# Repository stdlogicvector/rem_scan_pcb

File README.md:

# rem_scan_pcb

## An open source scan controller for SEMs

- Firmware: https://github.com/stdlogicvector/rem_scan
- GUI: https://github.com/stdlogicvector/rem_scan_gui

This PCB features two 16bit DACs to steer the electron beam of an SEM and two 16bit ADCs to acquire the image signal from up to two detectors.

It can be controlled via USB. The FTDI chip provides a virtual comport, a fast FIFO connection and a JTAG port for flashing the gateware.
Currently, only the serial port is supported in the gateware and the GUI.

Additionally, a VGA monitor can be connected for a live view of the image.
On PCBv1, only the internal blockram is used. This limits the resolution to 100x75 pixels. The image is upscaled to 800x600.

PCBv2 has external RAM and allows a native resolution of 800x600.

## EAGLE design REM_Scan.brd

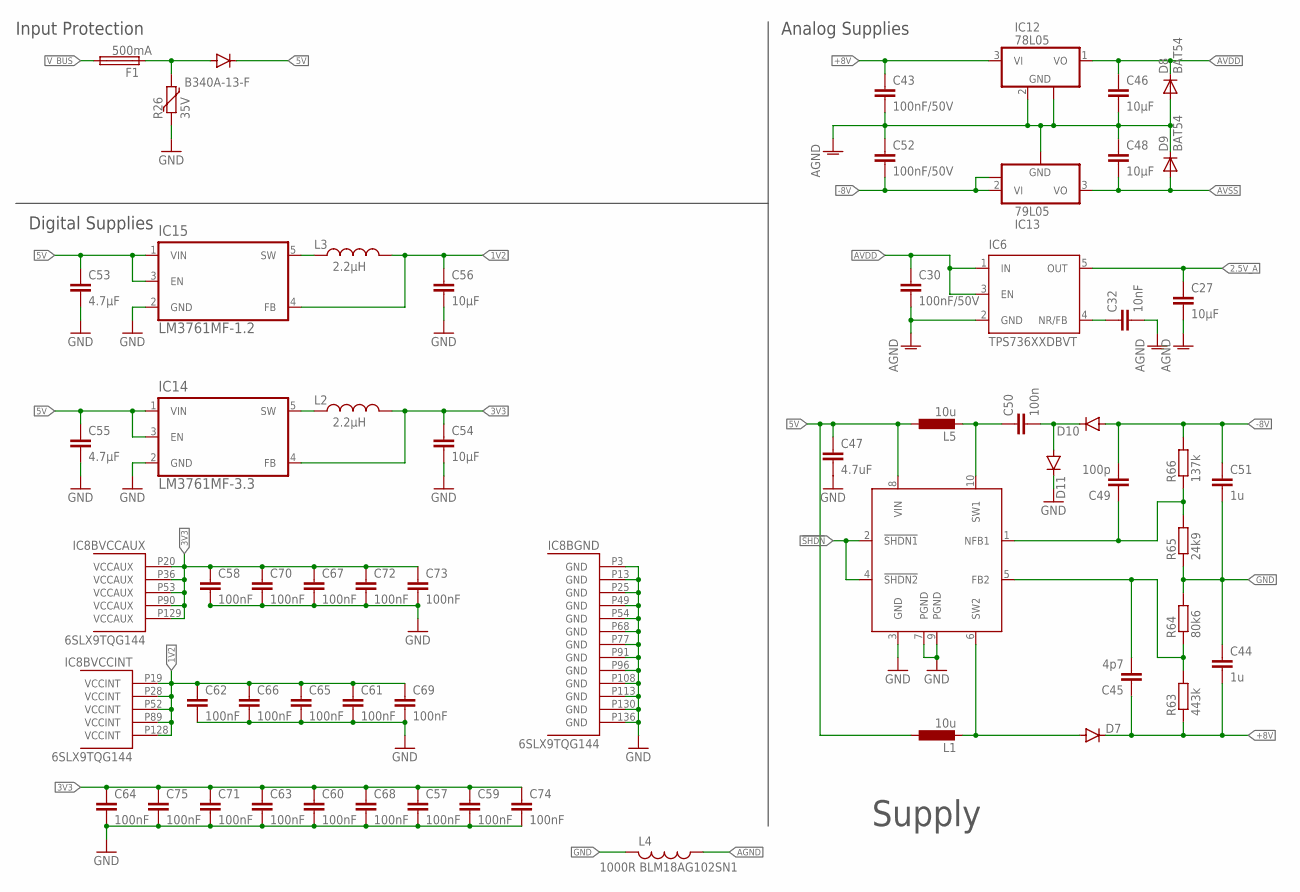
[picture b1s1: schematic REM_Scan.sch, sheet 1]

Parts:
C27, C46, C48: 10µF; C0603; FARNELL 2497051
C30, C43, C52: 100nF/50V; C0603
C32: 10nF; C0603
C44, C51: 1u; C1206; DIGIKEY 587-5596-1-ND
C45: 4p7; C0603
C47: 4.7uF; C3225
C49: 100p; C0603
C50: 100n; C0603
C53, C55: 4.7µF; C0603
C54, C56: 10µF; C0603
C57, C58, C59, C60, C61, C62, C63, C64, C65, C66, C67, C68, C69, C70, C71, C72, C73, C74, C75: 100nF; C0603
D3: B340A-13-F; DO214AA; FARNELL 1843668
D7, D10, D11: DIODE-SOD323-W; SOD323-W; DIGIKEY 1514-CMDSH05-4TRPBFREECT-ND
D8, D9: BAT54; SOD323-W; FARNELL 1459033
F1: 500mA; 1812; DIGIKEY F8132CT-ND
IC6: TPS736XXDBVT; SOT23-DBV
IC8: 6SLX9TQG144; TQ144; DIGIKEY 122-1747-ND
IC12: 78L05; SOT89; FARNELL 1366573
IC13: 79L05; SOT89; FARNELL 1467770
IC14: LM3761MF-3.3; SOT95P284X122-5N; FARNELL 1685767
IC15: LM3761MF-1.2; SOT95P284X122-5N; FARNELL 1685653
IC16: LT1945; MSOP10; DIGIKEY 505-LT1945EMS#PBF-ND
L1, L5: 10u; L3225P; DIGIKEY 445-174925-1-ND
L2, L3: 2.2µH; SO3314; FARNELL 2457514
L4: 1000R BLM18AG102SN1; L2012C; FARNELL 1515671
R26: 35V; R1206; DIGIKEY 118-ZV25K1206201NIR1CT-ND
R63: 443k; R0603
R64: 80k6; R0603
R65: 24k9; R0603
R66: 137k; R0603

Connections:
1V2: C56.1, C61.1, C62.1, C65.1, C66.1, C69.1, IC8.P19 (VCCINT), IC8.P28 (VCCINT), IC8.P52 (VCCINT), IC8.P89 (VCCINT), IC8.P128 (VCCINT), IC15.4 (FB), L3.2
2.5V_A: C27.1, IC6.5 (OUT); also elsewhere on the board
3V3: C54.1, C57.1, C58.1, C59.1, C60.1, C63.1, C64.1, C67.1, C68.1, C70.1, C71.1, C72.1, C73.1, C74.1, C75.1, IC8.P20 (VCCAUX), IC8.P36 (VCCAUX), IC8.P53 (VCCAUX), IC8.P90 (VCCAUX), IC8.P129 (VCCAUX), IC14.4 (FB), L2.2; also elsewhere on the board
5V: C47.1, C53.1, C55.1, D3.C, IC14.1 (VIN), IC14.3 (EN), IC15.1 (VIN), IC15.3 (EN), IC16.8 (VIN), L1.1, L5.1; also elsewhere on the board
!SHDN: IC16.2 (!SHDN1), IC16.4 (!SHDN2); also elsewhere on the board
+8V: C43.1, C44.2, C45.1, D7.C, IC12.3 (VI), R63.1; also elsewhere on the board
-8V: C49.2, C51.1, C52.2, D10.A, IC13.2 (VI), IC13.2@1 (VIN), R66.2
AGND: C27.2, C30.2, C32.2, C43.2, C46.2, C48.1, C52.1, D8.A, D9.C, IC6.2 (GND), IC12.2 (GND), IC12.2@1 (GND), IC13.1 (GND), L4.1; also elsewhere on the board
AVDD: C30.1, C46.1, D8.C, IC6.1 (IN), IC6.3 (EN), IC12.1 (VO); also elsewhere on the board
AVSS: C48.2, D9.A, IC13.3 (VO); also elsewhere on the board
GND: C44.1, C47.2, C51.2, C53.2, C54.2, C55.2, C56.2, C57.2, C58.2, C59.2, C60.2, C61.2, C62.2, C63.2, C64.2, C65.2, C66.2, C67.2, C68.2, C69.2, C70.2, C71.2, C72.2, C73.2, C74.2, C75.2, D11.C, IC8.P3 (GND), IC8.P13 (GND), IC8.P25 (GND), IC8.P49 (GND), IC8.P54 (GND), IC8.P68 (GND), IC8.P77 (GND), IC8.P91 (GND), IC8.P96 (GND), IC8.P108 (GND), IC8.P113 (GND), IC8.P130 (GND), IC8.P136 (GND), IC14.2 (GND), IC15.2 (GND), IC16.3 (GND), IC16.7 (PGND), IC16.9 (PGND), L4.2, R26.1, R64.2, R65.1; also elsewhere on the board
unnamed: IC15.5 (SW), L3.1
unnamed: C32.1, IC6.4 (NR/FB)
unnamed: C50.1, IC16.10 (SW1), L5.2
unnamed: C50.2, D10.C, D11.A
unnamed: D7.A, IC16.6 (SW2), L1.2
unnamed: C49.1, IC16.1 (NFB1), R65.2, R66.1
unnamed: C45.2, IC16.5 (FB2), R63.2, R64.1
unnamed: IC14.5 (SW), L2.1
SUPPLY_SEC: D3.A, F1.1, R26.2
V_BUS: F1.2; also elsewhere on the board

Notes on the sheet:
Input Protection
Supply
Digital Supplies
Analog Supplies

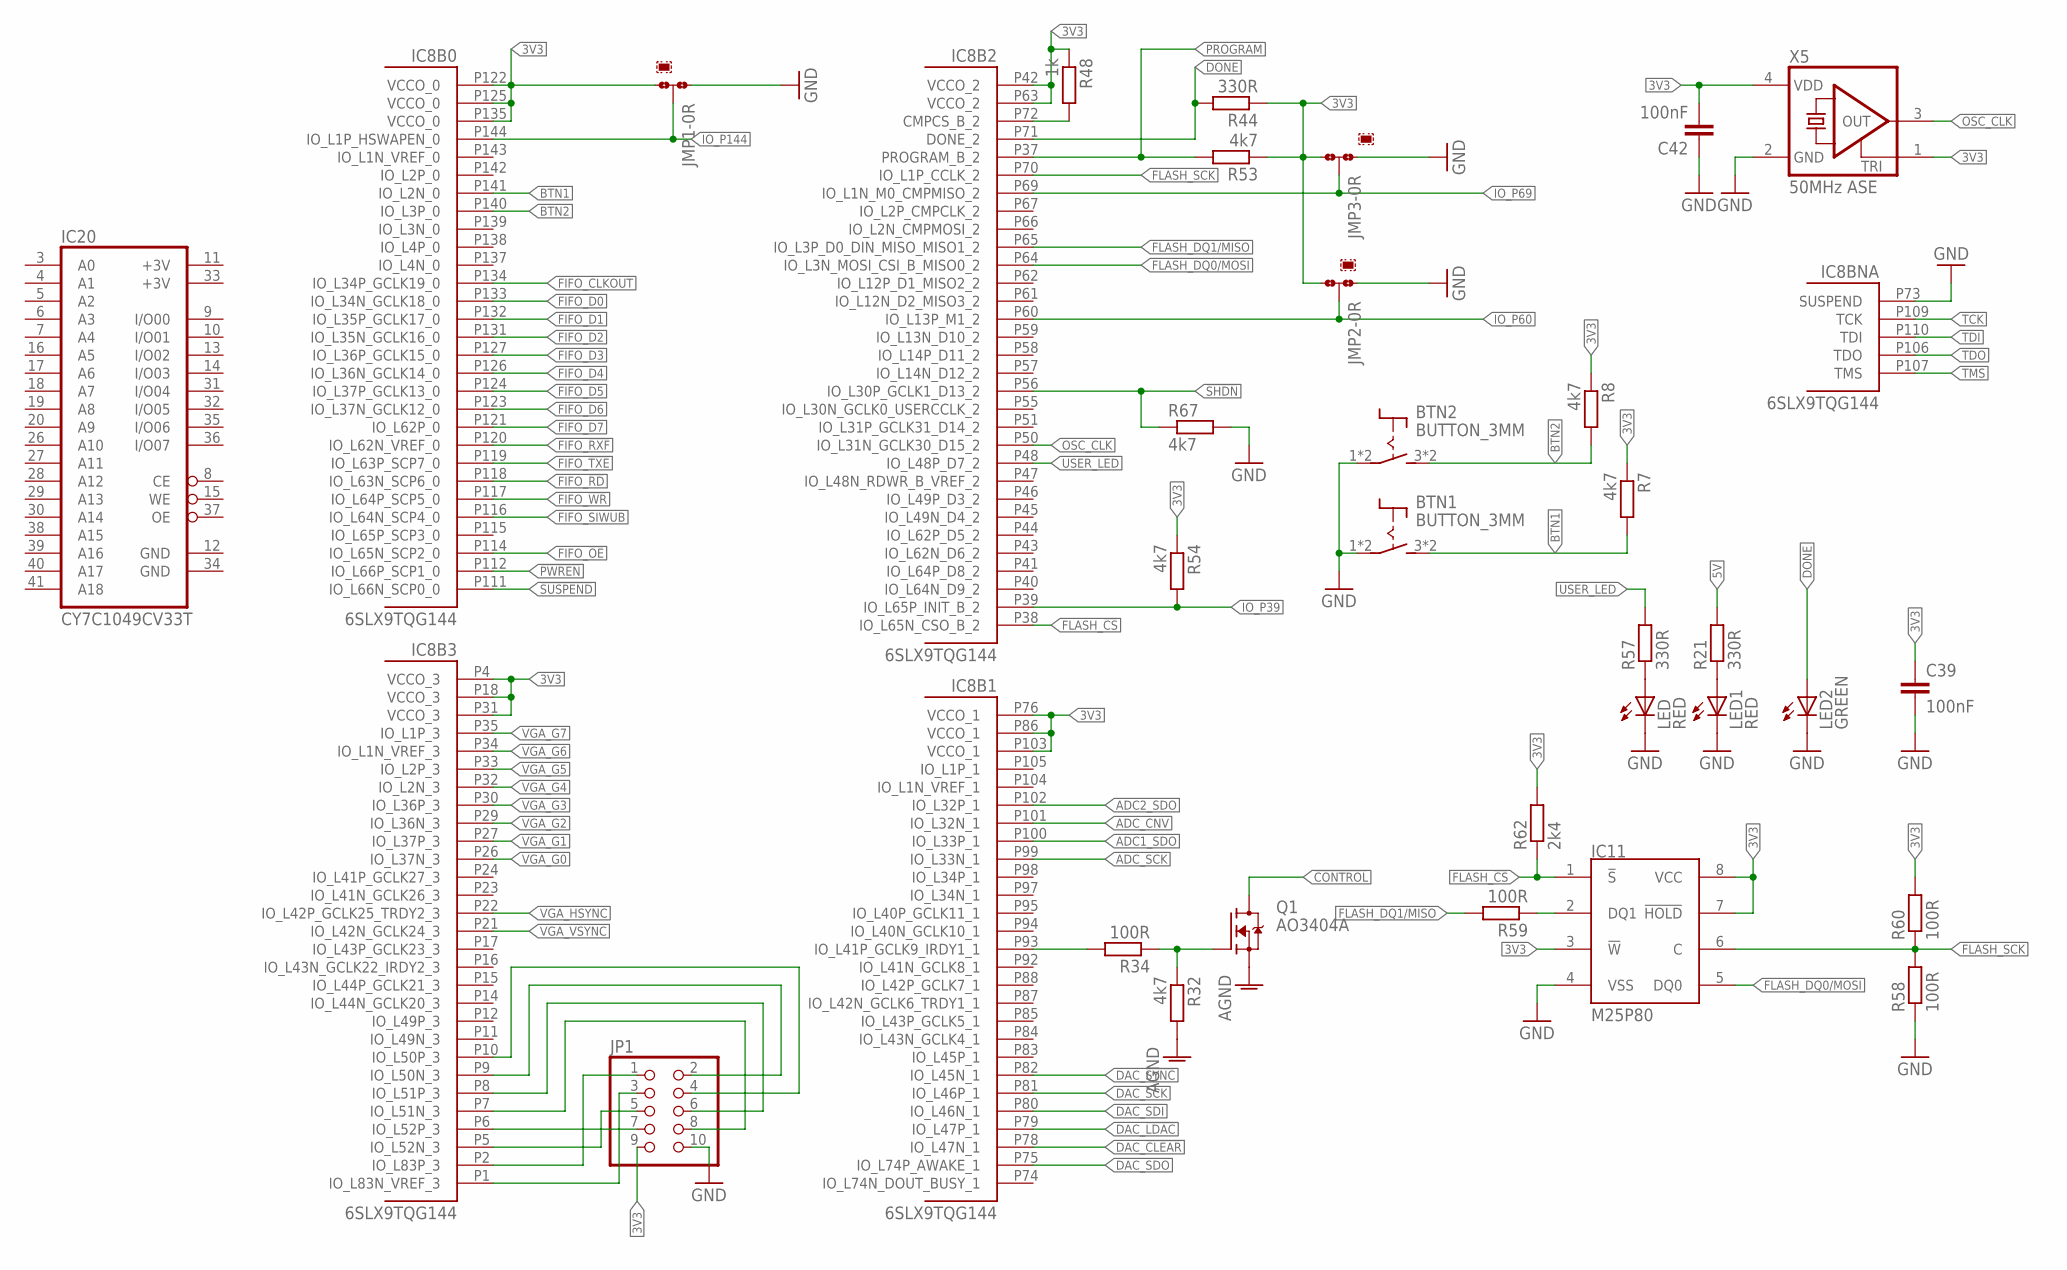
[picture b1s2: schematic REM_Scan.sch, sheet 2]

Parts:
BTN1, BTN2: BUTTON_3MM
C39, C42: 100nF; C0603
IC8: 6SLX9TQG144; TQ144; DIGIKEY 122-1747-ND
IC11: M25P80; SO-08
IC20: CY7C1049CV33T; TSOPII-Z44
JMP1, JMP2, JMP3: 1k; A0R-JMP
JP1: PINHD-2X5; 2X05
LED, LED1: RED; CHIP-LED0603; FARNELL 1685068
LED2: GREEN; CHIP-LED0603; FARNELL 1685068
Q1: AO3404A; SOT23; LCSC C30010
R7, R8, R32, R53, R54, R67: 4k7; R0603
R21, R44, R57: 330R; R0603
R34, R58, R59, R60: 100R; R0603
R48: 1k; R0603
R62: 2k4; R0603
X5: 50MHz ASE; ASE; DIGIKEY 535-9577-1-ND

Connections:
3V3: C39.1, C42.2, IC8.P4 (VCCO_3), IC8.P18 (VCCO_3), IC8.P31 (VCCO_3), IC8.P42 (VCCO_2), IC8.P63 (VCCO_2), IC8.P76 (VCCO_1), IC8.P86 (VCCO_1), IC8.P103 (VCCO_1), IC8.P122 (VCCO_0), IC8.P125 (VCCO_0), IC8.P135 (VCCO_0), IC11.3 (!W), IC11.7 (!HOLD), IC11.8 (VCC), JMP1.3, JMP2.3, JMP3.3, JP1.9, R7.1, R8.1, R44.1, R48.1, R53.1, R54.1, R60.2, R62.2, X5.1 (TRI), X5.4 (VDD); also elsewhere on the board
5V: R21.2; also elsewhere on the board
!CONTROL: Q1.3 (D); also elsewhere on the board
!PWREN: IC8.P112 (IO_L66P_SCP1_0); also elsewhere on the board
!SHDN: IC8.P56 (IO_L30P_GCLK1_D13_2), R67.1; also elsewhere on the board
!SUSPEND: IC8.P111 (IO_L66N_SCP0_0); also elsewhere on the board
+3V: IC20.11 (+3V), IC20.33 (+3V)
ADC1_SDO: IC8.P100 (IO_L33P_1); also elsewhere on the board
ADC2_SDO: IC8.P102 (IO_L32P_1); also elsewhere on the board
ADC_CNV: IC8.P101 (IO_L32N_1); also elsewhere on the board
ADC_SCK: IC8.P99 (IO_L33N_1); also elsewhere on the board
AGND: Q1.2 (S), R32.2; also elsewhere on the board
BTN1: BTN1.3 (S), BTN1.4 (S), IC8.P141 (IO_L2N_0), R7.2
BTN2: BTN2.3 (S), BTN2.4 (S), IC8.P140 (IO_L3P_0), R8.2
DAC_!CLEAR: IC8.P78 (IO_L47N_1); also elsewhere on the board
DAC_!LDAC: IC8.P79 (IO_L47P_1); also elsewhere on the board
DAC_!SYNC: IC8.P82 (IO_L45N_1); also elsewhere on the board
DAC_SCK: IC8.P81 (IO_L46P_1); also elsewhere on the board
DAC_SDI: IC8.P80 (IO_L46N_1); also elsewhere on the board
DAC_SDO: IC8.P75 (IO_L74P_AWAKE_1); also elsewhere on the board
DONE: IC8.P71 (DONE_2), LED2.A, R44.2
FIFO_!OE: IC8.P114 (IO_L65N_SCP2_0); also elsewhere on the board
FIFO_!RD: IC8.P118 (IO_L63N_SCP6_0); also elsewhere on the board
FIFO_!RXF: IC8.P120 (IO_L62N_VREF_0); also elsewhere on the board
FIFO_!TXE: IC8.P119 (IO_L63P_SCP7_0); also elsewhere on the board
FIFO_!WR: IC8.P117 (IO_L64P_SCP5_0); also elsewhere on the board
FIFO_CLKOUT: IC8.P134 (IO_L34P_GCLK19_0); also elsewhere on the board
FIFO_D0: IC8.P133 (IO_L34N_GCLK18_0); also elsewhere on the board
FIFO_D1: IC8.P132 (IO_L35P_GCLK17_0); also elsewhere on the board
FIFO_D2: IC8.P131 (IO_L35N_GCLK16_0); also elsewhere on the board
FIFO_D3: IC8.P127 (IO_L36P_GCLK15_0); also elsewhere on the board
FIFO_D4: IC8.P126 (IO_L36N_GCLK14_0); also elsewhere on the board
FIFO_D5: IC8.P124 (IO_L37P_GCLK13_0); also elsewhere on the board
FIFO_D6: IC8.P123 (IO_L37N_GCLK12_0); also elsewhere on the board
FIFO_D7: IC8.P121 (IO_L62P_0); also elsewhere on the board
FIFO_SIWUB: IC8.P116 (IO_L64N_SCP4_0); also elsewhere on the board
FLASH_!CS: IC8.P38 (IO_L65N_CSO_B_2), IC11.1 (!S), R62.1
FLASH_DQ0/MOSI: IC8.P64 (IO_L3N_MOSI_CSI_B_MISO0_2), IC11.5 (DQ0)
FLASH_DQ1/MISO: IC8.P65 (IO_L3P_D0_DIN_MISO_MISO1_2), R59.2
FLASH_SCK: IC8.P70 (IO_L1P_CCLK_2), IC11.6 (C), R58.2, R60.1
GND: BTN1.1, BTN1.2, BTN2.1, BTN2.2, C39.2, C42.1, IC8.P73 (SUSPEND), IC11.4 (VSS), IC20.12 (GND), IC20.34 (GND), JMP1.1, JMP2.1, JMP3.1, JP1.10, LED.C, LED1.C, LED2.C, R58.1, R67.2, X5.2 (GND); also elsewhere on the board
IO_P39: IC8.P39 (IO_L65P_INIT_B_2), R54.2
IO_P60: IC8.P60 (IO_L13P_M1_2), JMP2.2
IO_P69: IC8.P69 (IO_L1N_M0_CMPMISO_2), JMP3.2
IO_P144: IC8.P144 (IO_L1P_HSWAPEN_0), JMP1.2
unnamed: IC11.2 (DQ1), R59.1
unnamed: LED1.A, R21.1
unnamed: Q1.1 (G), R32.1, R34.1
unnamed: IC8.P72 (CMPCS_B_2), R48.2
unnamed: IC8.P93 (IO_L41P_GCLK9_IRDY1_1), R34.2
unnamed: LED.A, R57.1
unnamed: IC8.P6 (IO_L52P_3), JP1.7
unnamed: IC8.P7 (IO_L51N_3), JP1.8
unnamed: IC8.P5 (IO_L52N_3), JP1.5
unnamed: IC8.P8 (IO_L51P_3), JP1.6
unnamed: IC8.P1 (IO_L83N_VREF_3), JP1.3
unnamed: IC8.P2 (IO_L83P_3), JP1.1
unnamed: IC8.P9 (IO_L50N_3), JP1.2
unnamed: IC8.P10 (IO_L50P_3), JP1.4
OSC_CLK: IC8.P50 (IO_L31N_GCLK30_D15_2), X5.3 (OUT)
PROGRAM: IC8.P37 (PROGRAM_B_2), R53.2
TCK: IC8.P109 (TCK); also elsewhere on the board
TDI: IC8.P110 (TDI); also elsewhere on the board
TDO: IC8.P106 (TDO); also elsewhere on the board
TMS: IC8.P107 (TMS); also elsewhere on the board
USER_LED: IC8.P48 (IO_L48P_D7_2), R57.2
VGA_G0: IC8.P26 (IO_L37N_3); also elsewhere on the board
VGA_G1: IC8.P27 (IO_L37P_3); also elsewhere on the board
VGA_G2: IC8.P29 (IO_L36N_3); also elsewhere on the board
VGA_G3: IC8.P30 (IO_L36P_3); also elsewhere on the board
VGA_G4: IC8.P32 (IO_L2N_3); also elsewhere on the board
VGA_G5: IC8.P33 (IO_L2P_3); also elsewhere on the board
VGA_G6: IC8.P34 (IO_L1N_VREF_3); also elsewhere on the board
VGA_G7: IC8.P35 (IO_L1P_3); also elsewhere on the board
VGA_HSYNC: IC8.P22 (IO_L42P_GCLK25_TRDY2_3); also elsewhere on the board
VGA_VSYNC: IC8.P21 (IO_L42N_GCLK24_3); also elsewhere on the board

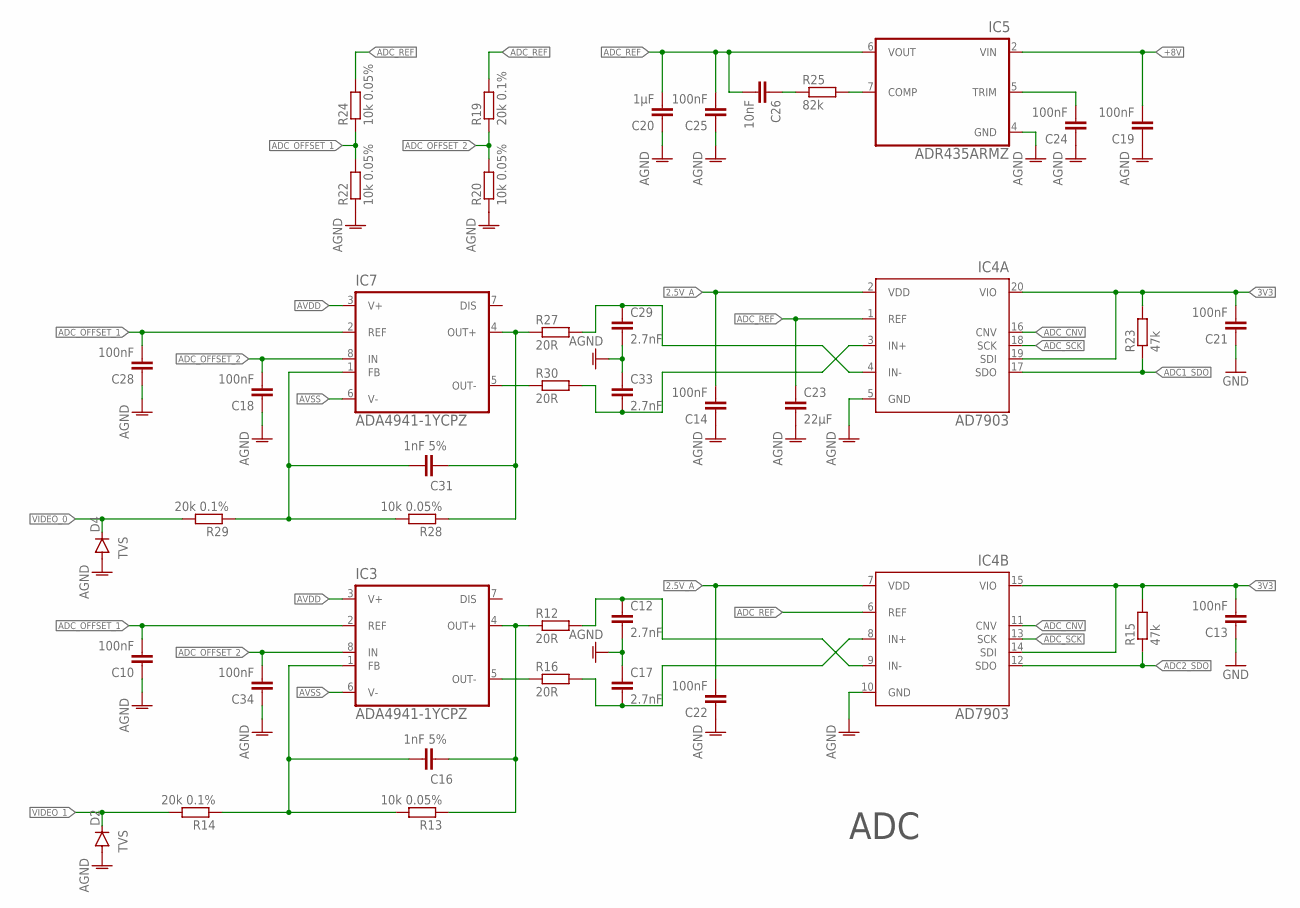
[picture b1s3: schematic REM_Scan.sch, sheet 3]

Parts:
C10, C13, C14, C18, C19, C21, C22, C24, C25, C28, C34: 100nF; C0603
C12, C17, C29, C33: 2.7nF; C0603K; FARNELL 1759094
C16, C31: 1nF 5%; C0603; FARNELL 1789718
C20: 1µF; C0603; FARNELL 2496835
C23: 22µF; C0805K; FARNELL 1845739
C26: 10nF; C0603
D2, D4: TVS; SOD123; DIGIKEY 641-1986-1-ND
IC3, IC7: ADA4941-1YCPZ; LFCSP_VD8_CP-8-2
IC4: AD7903; RQ-20
IC5: ADR435ARMZ; MSOP08
R12, R16, R27, R30: 20R; R0603; FARNELL 9330763
R13, R20, R22, R24, R28: 10k 0.05%; R0603; FARNELL 1688472
R14, R19, R29: 20k 0.1%; R0603; FARNELL 1717605
R15, R23: 47k; R0603; FARNELL 2141566
R25: 82k; R0603; FARNELL 9331573

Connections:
2.5V_A: C14.2, C22.2, IC4.2 (VDD), IC4.7 (VDD); also elsewhere on the board
3V3: C13.2, C21.2, IC4.14 (SDI), IC4.15 (VIO), IC4.19 (SDI), IC4.20 (VIO), R15.2, R23.2; also elsewhere on the board
+8V: C19.2, IC5.2 (VIN); also elsewhere on the board
ADC1_SDO: IC4.17 (SDO), R23.1; also elsewhere on the board
ADC2_SDO: IC4.12 (SDO), R15.1; also elsewhere on the board
ADC_CNV: IC4.11 (CNV), IC4.16 (CNV); also elsewhere on the board
ADC_OFFSET_1: C10.2, C28.2, IC3.2 (REF), IC7.2 (REF), R22.2, R24.1
ADC_OFFSET_2: C18.2, C34.2, IC3.8 (IN), IC7.8 (IN), R19.1, R20.2
ADC_REF: C20.2, C23.1, C25.2, C26.2, IC4.1 (REF), IC4.6 (REF), IC5.6 (VOUT), R19.2, R24.2
ADC_SCK: IC4.13 (SCK), IC4.18 (SCK); also elsewhere on the board
AGND: C10.1, C12.2, C14.1, C17.1, C18.1, C19.1, C20.1, C22.1, C23.2, C24.1, C25.1, C28.1, C29.2, C33.1, C34.1, D2.A, D4.A, IC4.5 (GND), IC4.10 (GND), IC5.4 (GND), R20.1, R22.1; also elsewhere on the board
AVDD: IC3.3 (V+), IC7.3 (V+); also elsewhere on the board
AVSS: IC3.6 (V-), IC7.6 (V-); also elsewhere on the board
GND: C13.1, C21.1; also elsewhere on the board
unnamed: C12.1, IC4.9 (IN-), R12.2
unnamed: C17.2, IC4.8 (IN+), R16.2
unnamed: C31.1, IC7.4 (OUT+), R27.1, R28.1
unnamed: IC7.5 (OUT-), R30.1
unnamed: C29.1, IC4.4 (IN-), R27.2
unnamed: C33.2, IC4.3 (IN+), R30.2
unnamed: C16.1, IC3.4 (OUT+), R12.1, R13.1
unnamed: IC3.5 (OUT-), R16.1
unnamed: C24.2, IC5.5 (TRIM)
unnamed: IC5.7 (COMP), R25.2
unnamed: C26.1, R25.1
unnamed: C31.2, IC7.1 (FB), R28.2, R29.1
unnamed: C16.2, IC3.1 (FB), R13.2, R14.1
VIDEO_0: D4.C, R29.2; also elsewhere on the board
VIDEO_1: D2.C, R14.2; also elsewhere on the board

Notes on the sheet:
ADC

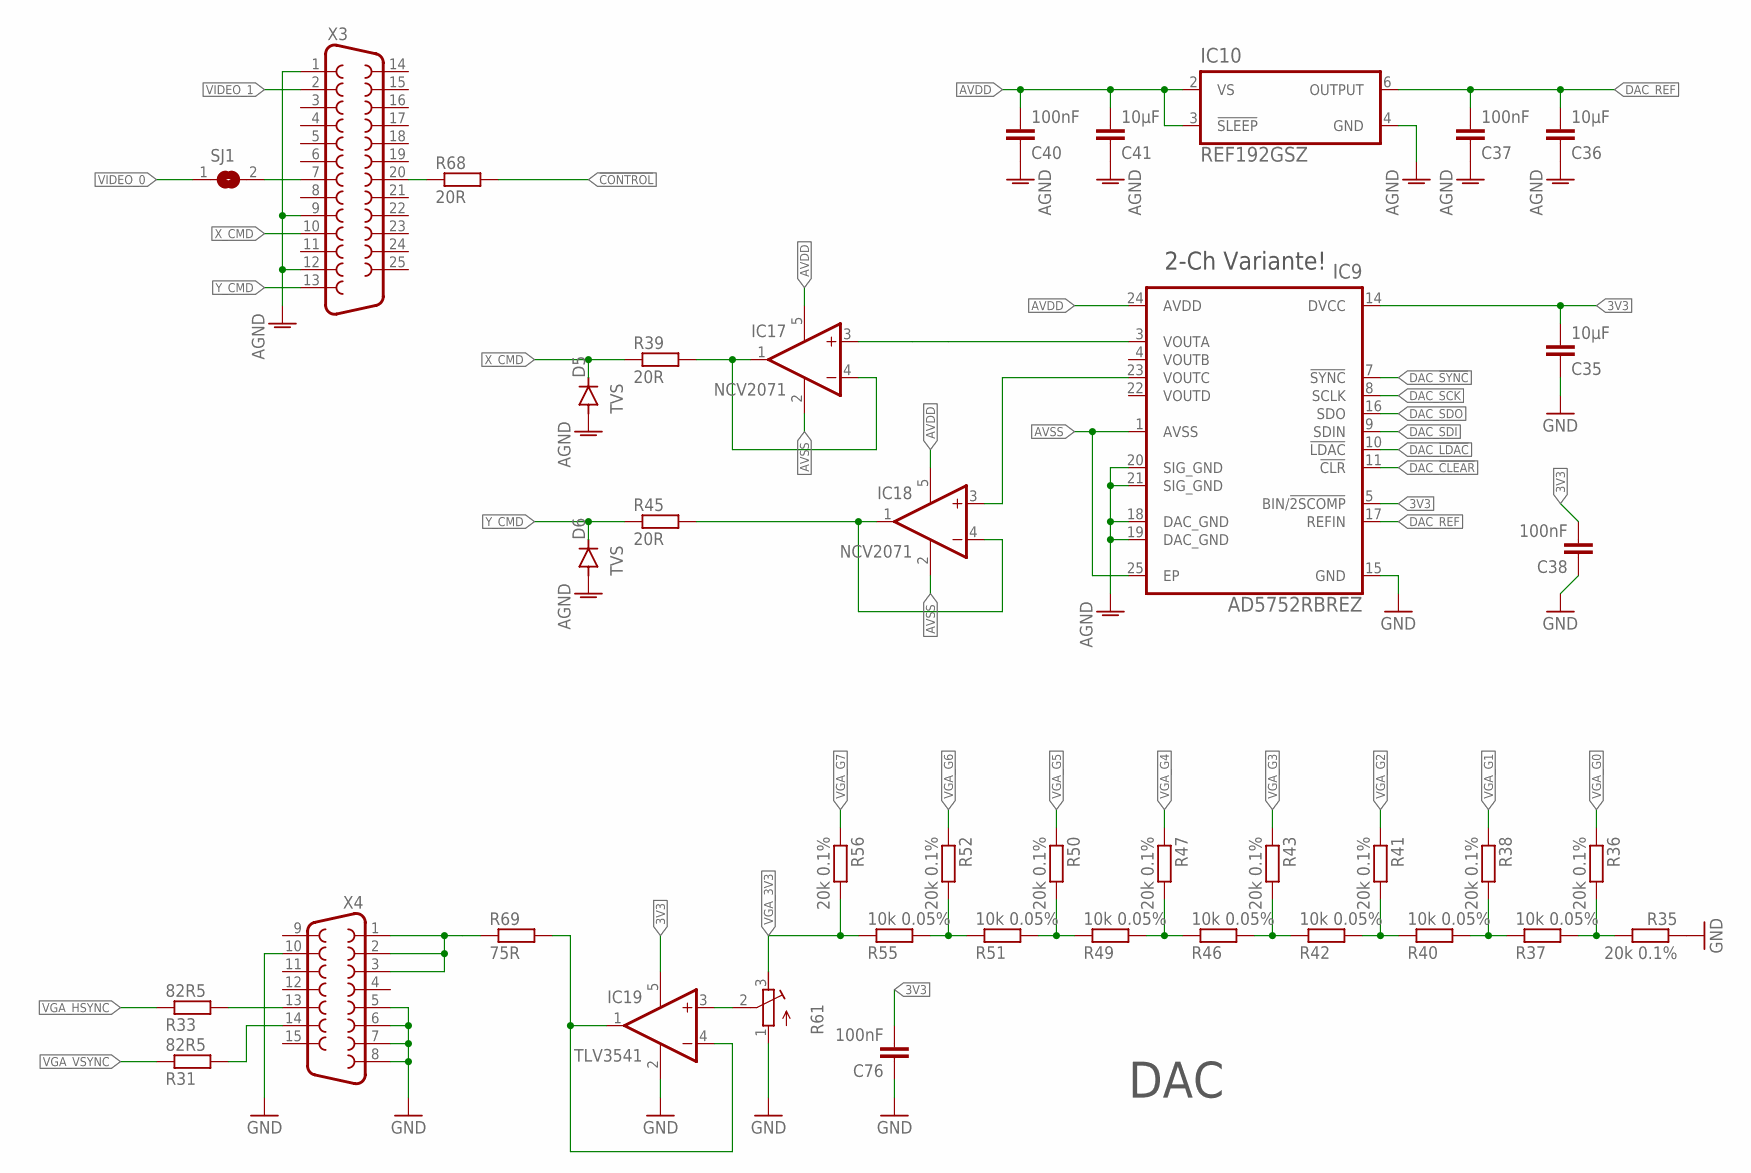
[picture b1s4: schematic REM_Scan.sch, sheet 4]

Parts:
C35, C36, C41: 10µF; C0603; FARNELL 2497051
C37, C38, C40, C76: 100nF; C0603
D5, D6: TVS; SOD123; DIGIKEY 641-1986-1-ND
IC9: AD5752RBREZ; SOP65P640X120-25N; MPN AD5752RBREZ; FARNELL 1786049
IC10: REF192GSZ; SOIC127P600X175-8N
IC17, IC18: NCV2071; SOT23-5; DIGIKEY NCV20071SN2T1GOSCT-ND
IC19: TLV3541; SOT23-5; DIGIKEY NCV20071SN2T1GOSCT-ND
R31, R33: 82R5; R0603
R35, R36, R38, R41, R43, R47, R50, R52, R56: 20k 0.1%; R0603; FARNELL 1717605
R37, R40, R42, R46, R49, R51, R55: 10k 0.05%; R0603; FARNELL 1688472
R39, R45, R68: 20R; R0603; FARNELL 9330763
R61: R-TRIMM3296W; RTRIM3296W
R69: 75R; R0603; FARNELL 9330763
SJ1: SJ
X3: F25HP
X4: F15HDH; HDF15H

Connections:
3V3: C35.2, C38.2, C76.2, IC9.5 (BIN/!2SCOMP), IC9.14 (DVCC), IC19.5 (V+); also elsewhere on the board
!CONTROL: R68.2; also elsewhere on the board
AGND: C36.1, C37.1, C40.1, C41.1, D5.A, D6.A, IC9.18 (DAC_GND), IC9.19 (DAC_GND), IC9.20 (SIG_GND), IC9.21 (SIG_GND), IC10.4 (GND), X3.1, X3.9, X3.12; also elsewhere on the board
AVDD: C40.2, C41.2, IC9.24 (AVDD), IC10.2 (VS), IC10.3 (!SLEEP), IC17.5 (V+), IC18.5 (V+); also elsewhere on the board
AVSS: IC9.1 (AVSS), IC9.25 (EP), IC17.2 (V-), IC18.2 (V-); also elsewhere on the board
DAC_!CLEAR: IC9.11 (!CLR); also elsewhere on the board
DAC_!LDAC: IC9.10 (!LDAC); also elsewhere on the board
DAC_!SYNC: IC9.7 (!SYNC); also elsewhere on the board
DAC_REF: C36.2, C37.2, IC9.17 (REFIN), IC10.6 (OUTPUT)
DAC_SCK: IC9.8 (SCLK); also elsewhere on the board
DAC_SDI: IC9.9 (SDIN); also elsewhere on the board
DAC_SDO: IC9.16 (SDO); also elsewhere on the board
GND: C35.1, C38.1, C76.1, IC9.15 (GND), IC19.2 (V-), R35.1, R61.1 (A), X4.5, X4.6, X4.7, X4.8, X4.10; also elsewhere on the board
unnamed: SJ1.2, X3.7
unnamed: R31.2, X4.14
unnamed: R69.1, X4.1, X4.2, X4.3
unnamed: R33.2, X4.13
unnamed: R35.2, R36.2, R37.2
unnamed: R37.1, R38.2, R40.2
unnamed: R40.1, R41.2, R42.2
unnamed: R42.1, R43.2, R46.2
unnamed: R46.1, R47.2, R49.2
unnamed: R49.1, R50.2, R51.2
unnamed: R51.1, R52.2, R55.2
unnamed: IC19.1 (OUT), IC19.4 (-IN), R69.2
unnamed: IC17.1 (OUT), IC17.4 (-IN), R39.2
unnamed: IC9.3 (VOUTA), IC17.3 (+IN)
unnamed: IC18.1 (OUT), IC18.4 (-IN), R45.2
unnamed: IC9.23 (VOUTC), IC18.3 (+IN)
unnamed: R68.1, X3.20
unnamed: IC19.3 (+IN), R61.2 (S)
VGA_3V3: R55.1, R56.2, R61.3 (E)
VGA_G0: R36.1; also elsewhere on the board
VGA_G1: R38.1; also elsewhere on the board
VGA_G2: R41.1; also elsewhere on the board
VGA_G3: R43.1; also elsewhere on the board
VGA_G4: R47.1; also elsewhere on the board
VGA_G5: R50.1; also elsewhere on the board
VGA_G6: R52.1; also elsewhere on the board
VGA_G7: R56.1; also elsewhere on the board
VGA_HSYNC: R33.1; also elsewhere on the board
VGA_VSYNC: R31.1; also elsewhere on the board
VIDEO_0: SJ1.1; also elsewhere on the board
VIDEO_1: X3.2; also elsewhere on the board
X_CMD: D5.C, R39.1, X3.10
Y_CMD: D6.C, R45.1, X3.13

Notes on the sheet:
DAC
2-Ch Variante!

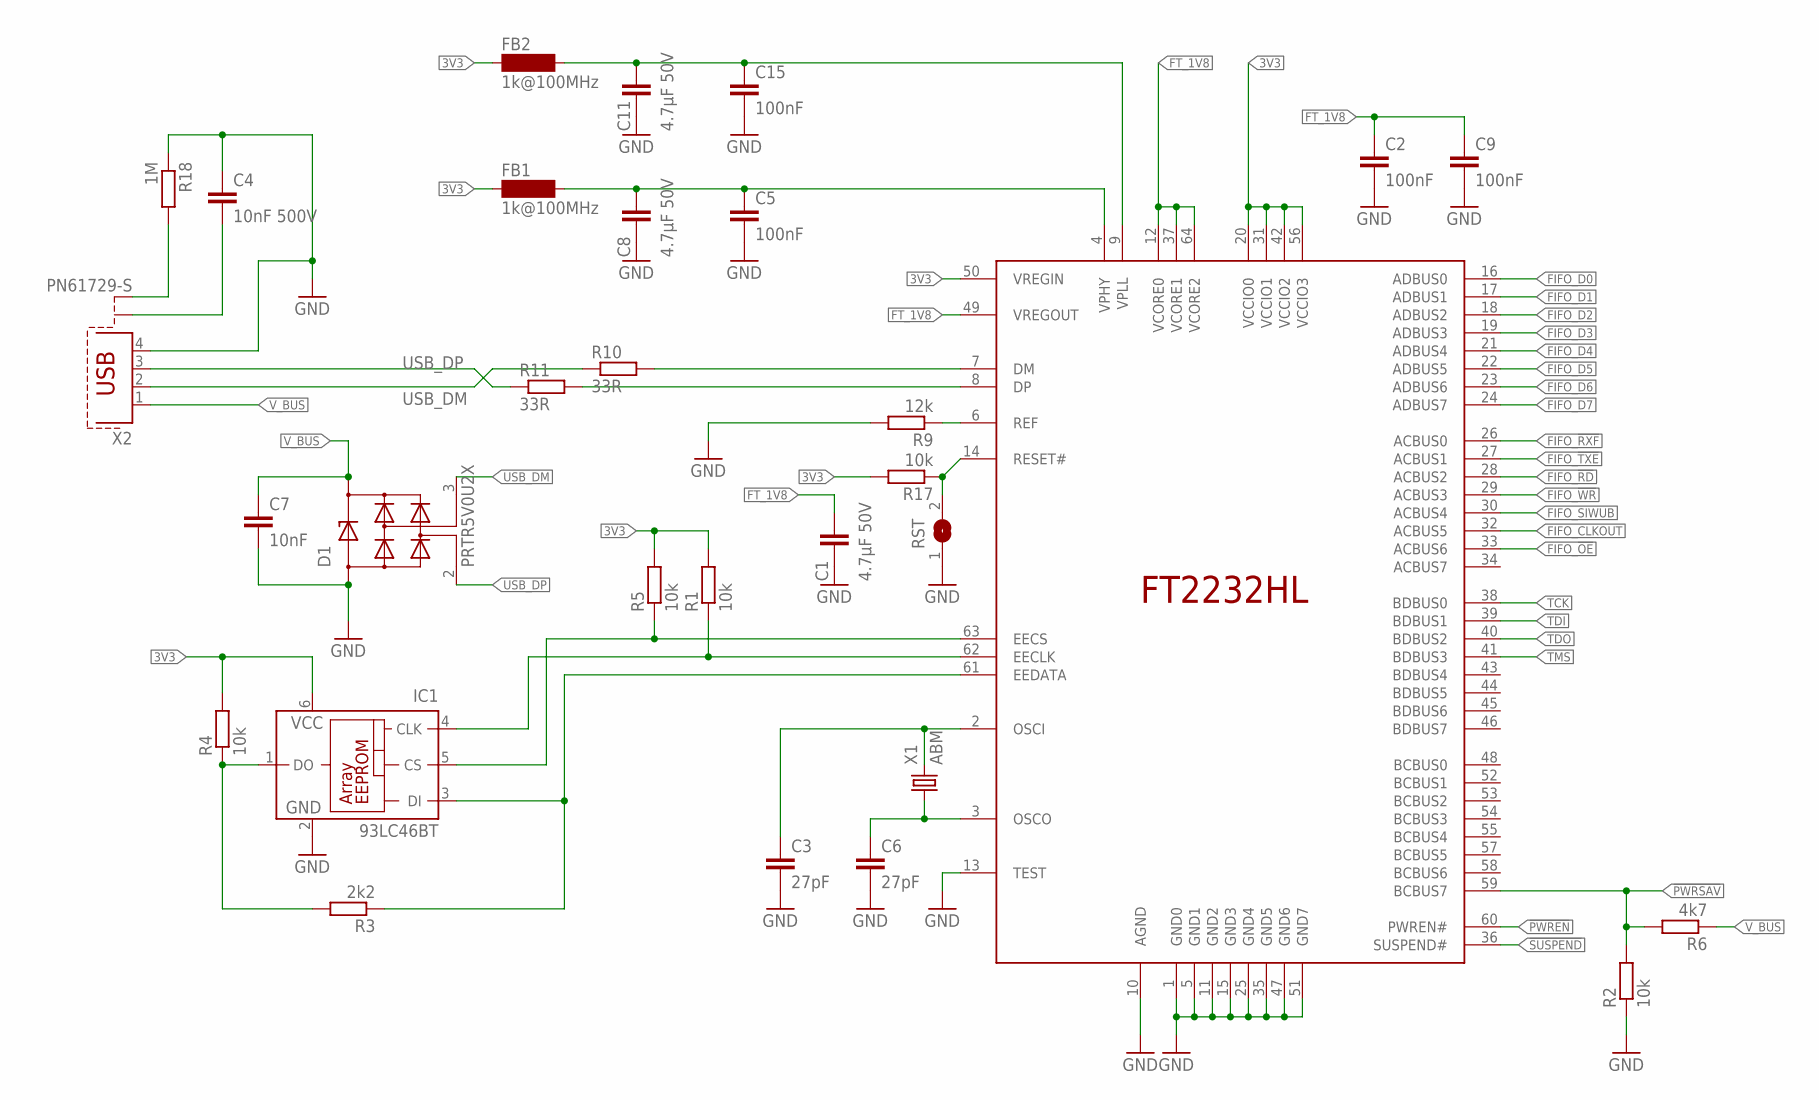
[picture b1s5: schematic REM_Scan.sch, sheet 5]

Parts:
C1, C8, C11: 4.7µF 50V; C0805
C2, C5, C9, C15: 100nF; C0603
C3, C6: 27pF; C0603
C4: 10nF 500V; C0805
C7: 10nF; C0603
D1: PRTR5V0U2X; SOT143; FARNELL 1524157
FB1, FB2: 1k@100MHz; SM-1206; FARNELL 1635759
IC1: 93LC46BT; SOT23-6; FARNELL 1556164
IC2: FT2232HL; LQFP64; FARNELL 1697461
R1, R2, R4, R5, R17: 10k; R0603
R3: 2k2; R0603
R6: 4k7; R0603
R9: 12k; R0603
R10, R11: 33R; R0603
R18: 1M; R0603
RST: SJS
X1: ABM; ASE; FARNELL 2308707
X2: PN61729-S

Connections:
3V3: FB1.1, FB2.1, IC1.6 (VCC), IC2.20 (VCCIO0), IC2.31 (VCCIO1), IC2.42 (VCCIO2), IC2.50 (VREGIN), IC2.56 (VCCIO3), R1.2, R4.2, R5.2, R17.2; also elsewhere on the board
!PWREN: IC2.60 (PWREN#); also elsewhere on the board
!PWRSAV: IC2.59 (BCBUS7), R2.2, R6.2
!SUSPEND: IC2.36 (SUSPEND#); also elsewhere on the board
FIFO_!OE: IC2.33 (ACBUS6); also elsewhere on the board
FIFO_!RD: IC2.28 (ACBUS2); also elsewhere on the board
FIFO_!RXF: IC2.26 (ACBUS0); also elsewhere on the board
FIFO_!TXE: IC2.27 (ACBUS1); also elsewhere on the board
FIFO_!WR: IC2.29 (ACBUS3); also elsewhere on the board
FIFO_CLKOUT: IC2.32 (ACBUS5); also elsewhere on the board
FIFO_D0: IC2.16 (ADBUS0); also elsewhere on the board
FIFO_D1: IC2.17 (ADBUS1); also elsewhere on the board
FIFO_D2: IC2.18 (ADBUS2); also elsewhere on the board
FIFO_D3: IC2.19 (ADBUS3); also elsewhere on the board
FIFO_D4: IC2.21 (ADBUS4); also elsewhere on the board
FIFO_D5: IC2.22 (ADBUS5); also elsewhere on the board
FIFO_D6: IC2.23 (ADBUS6); also elsewhere on the board
FIFO_D7: IC2.24 (ADBUS7); also elsewhere on the board
FIFO_SIWUB: IC2.30 (ACBUS4); also elsewhere on the board
FT_1V8: C1.1, C2.1, C9.1, IC2.12 (VCORE0), IC2.37 (VCORE1), IC2.49 (VREGOUT), IC2.64 (VCORE2)
GND: C1.2, C2.2, C3.2, C4.1, C5.2, C6.2, C7.2, C8.2, C9.2, C11.2, C15.2, D1.1 (GND), IC1.2 (GND), IC2.1 (GND0), IC2.5 (GND1), IC2.10 (AGND), IC2.11 (GND2), IC2.13 (TEST), IC2.15 (GND3), IC2.25 (GND4), IC2.35 (GND5), IC2.47 (GND6), IC2.51 (GND7), R2.1, R9.2, R18.1, RST.1, X1.2 (GND), X1.4 (GND), X2.4; also elsewhere on the board
unnamed: R18.2, X2.S2
unnamed: C4.2, X2.S1
unnamed: IC2.7 (DM), R10.2
unnamed: IC2.8 (DP), R11.2
unnamed: IC1.5 (CS), IC2.63 (EECS), R5.1
unnamed: IC1.4 (CLK), IC2.62 (EECLK), R1.1
unnamed: IC1.3 (DI), IC2.61 (EEDATA), R3.1
unnamed: C3.1, IC2.2 (OSCI), X1.3 (2)
unnamed: C6.1, IC2.3 (OSCO), X1.1
unnamed: IC1.1 (DO), R3.2, R4.1
unnamed: IC2.14 (RESET#), R17.1, RST.2
unnamed: IC2.6 (REF), R9.1
TCK: IC2.38 (BDBUS0); also elsewhere on the board
TDI: IC2.39 (BDBUS1); also elsewhere on the board
TDO: IC2.40 (BDBUS2); also elsewhere on the board
TMS: IC2.41 (BDBUS3); also elsewhere on the board
USB_DM: D1.3 (IO2), R10.1, X2.2
USB_DP: D1.2 (IO1), R11.1, X2.3
VPHY: C5.1, C8.1, FB1.2, IC2.4 (VPHY)
VPLL: C11.1, C15.1, FB2.2, IC2.9 (VPLL)
V_BUS: C7.1, D1.4 (VCC), R6.1, X2.1; also elsewhere on the board

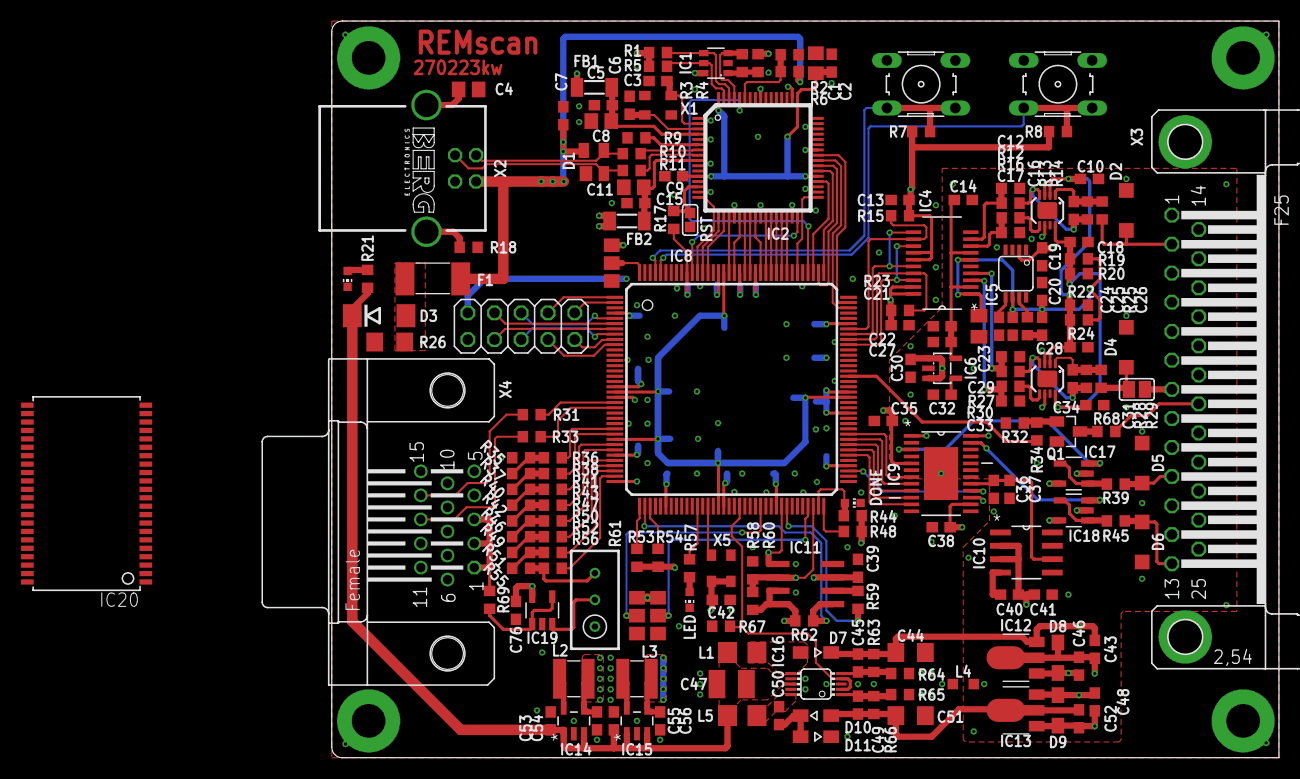
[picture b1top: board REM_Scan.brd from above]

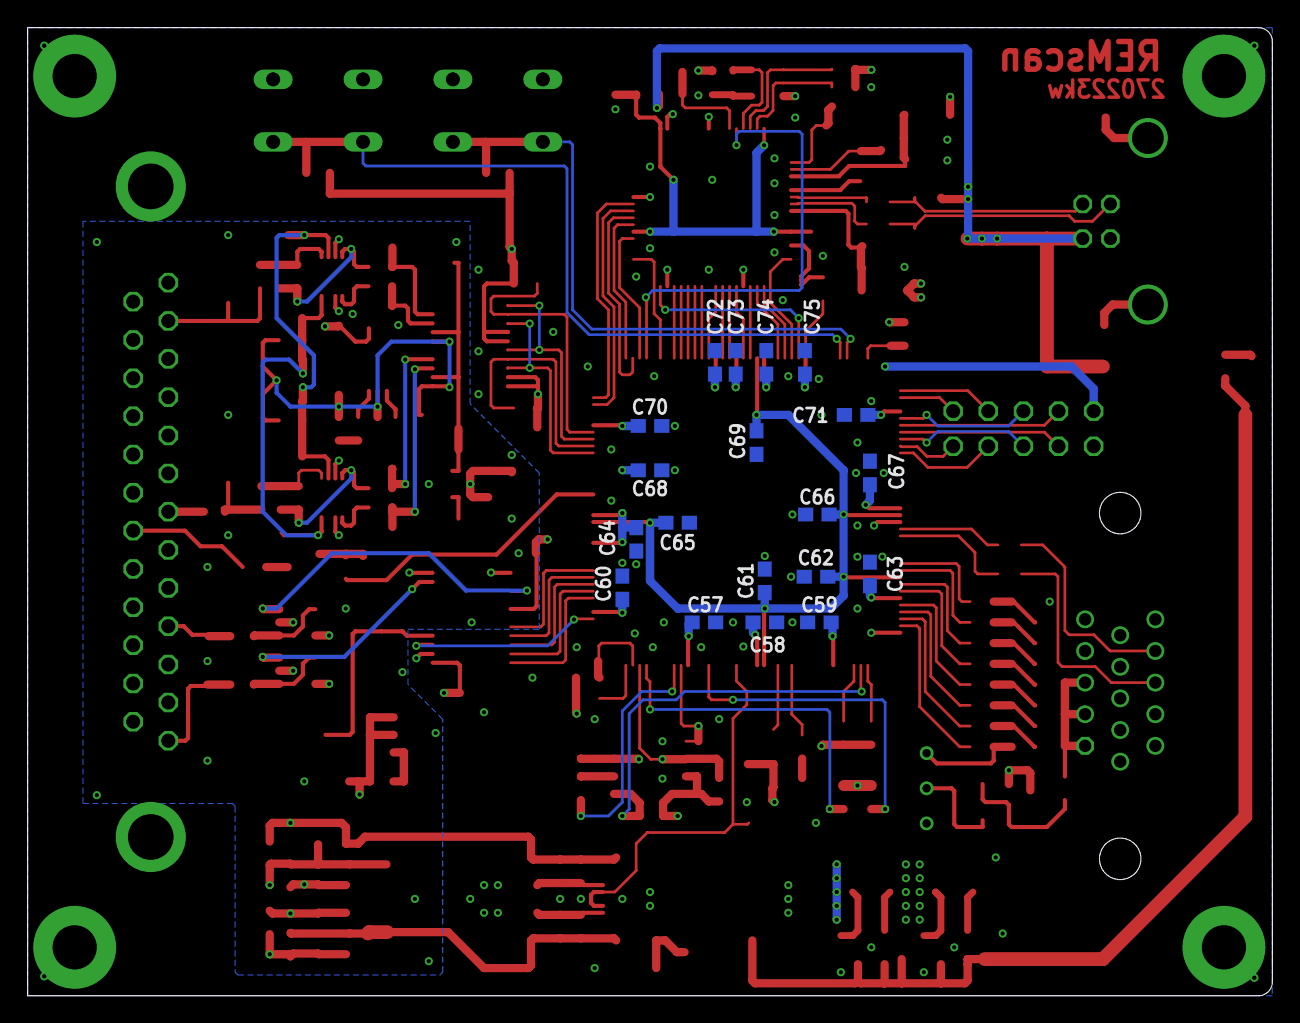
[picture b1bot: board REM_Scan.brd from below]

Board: 4 copper layers, 90.0 x 70.0 mm, 201 parts (19 on the bottom side), 150 nets.

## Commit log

2024-01-02 Add PDFs of schematics
